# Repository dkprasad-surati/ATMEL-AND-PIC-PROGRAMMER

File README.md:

# ATMEL-AND-PIC-PROGRAMMER
PORTABLE PROGRAMMER

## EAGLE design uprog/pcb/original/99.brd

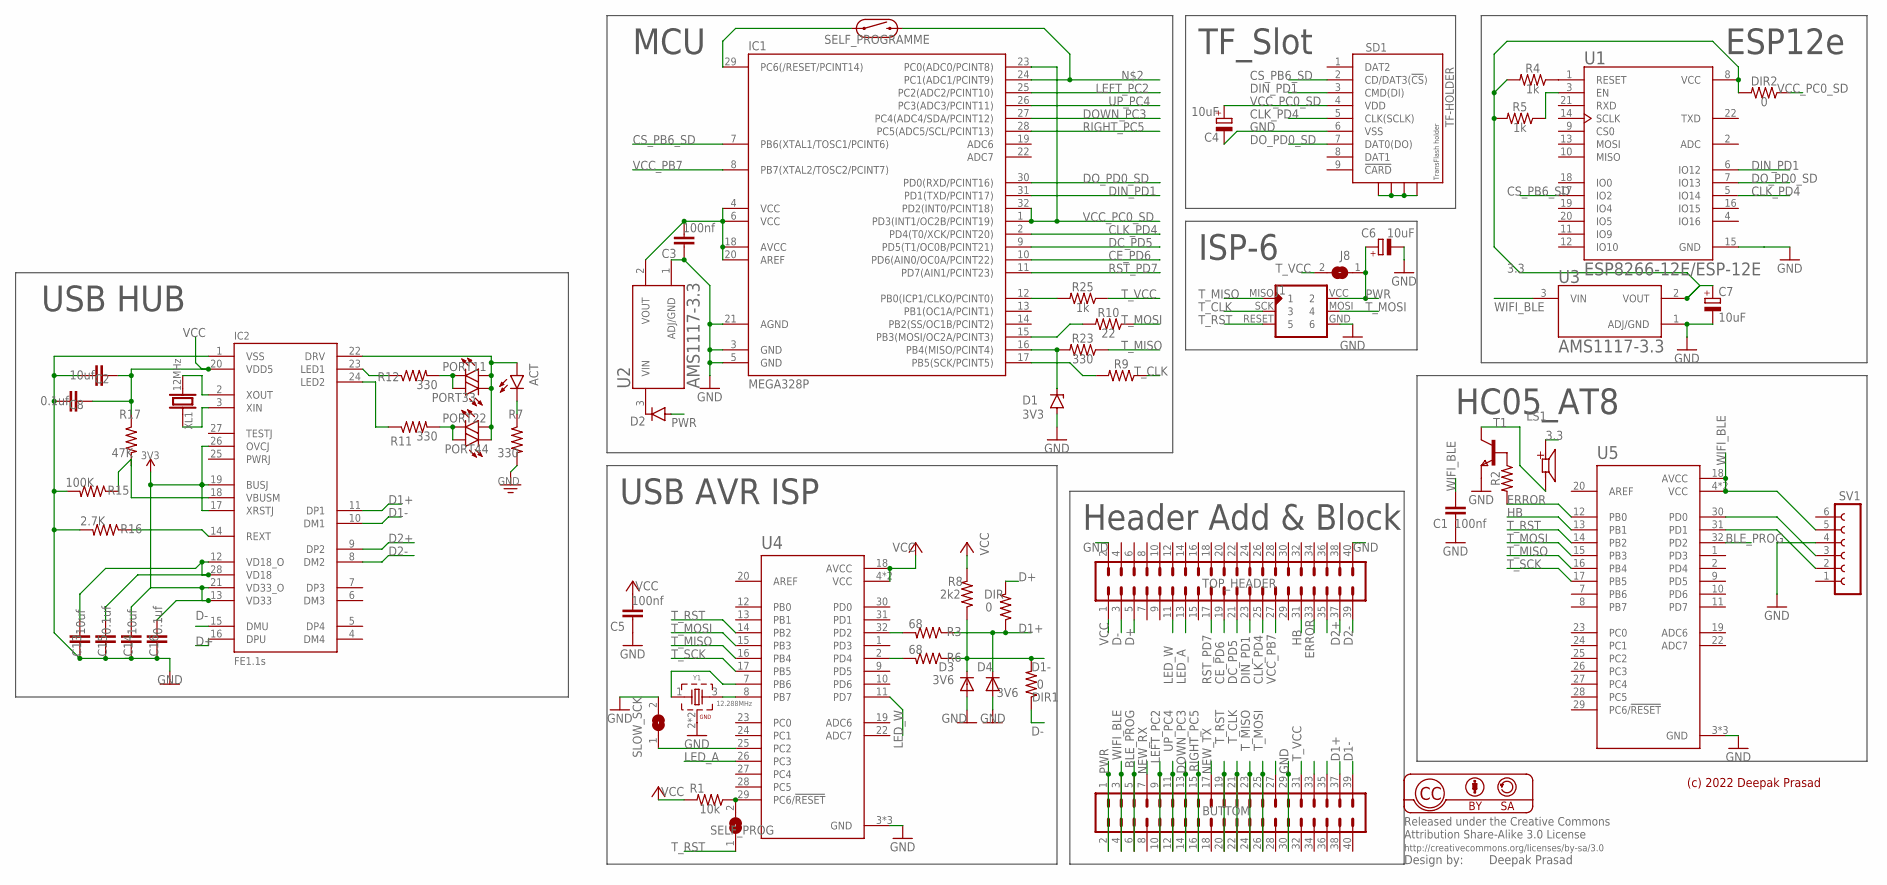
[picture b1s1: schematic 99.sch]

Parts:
ACT: LED1206; LED-1206
BUTTOM: MA20-2
C1, C3, C5: 100nf; C1206
C2, C13, C14: 10uf; C1206
C4, C6, C7: 10uF; C/6032-28R
C8, C15, C16: 0.1uf; C1206
D1: 3V3; SOD80C
D2: DIODE-DO214AC; DO214AC
D3, D4: 3V6; SMA-DIODE
DIR, DIR1, DIR2: 0; RESC3216X70
IC1: MEGA328P; TQFP32-08
IC2: FE1.1S; FE1.1S_SSOP-28
J1: AVR-ISP-6PINAVR-ISP-6PIN; AVR-ISP-6PIN
J8: SJW
LS1: CMT-8530S-SMT; CUI_CMT-8530S-SMT
PORT11, PORT22, PORT33, PORT44: LED1206; LED-1206
R1: 10k; RESC3216X70
R2, R9, R10: 22; RESC3216X70
R3, R6: 68; RESC3216X70
R4, R5, R25: 1k; RESC3216X70
R7, R11, R12, R23: 330; RESC3216X70
R8: 2k2; RESC3216X70
R15: 100K; RESC3216X70
R16: 2.7K; RESC3216X70
R17: 47K; RESC3216X70
SD1: TF-HOLDER; TF-PULL
SELF_PROG: SJW
SELF_PROGRAMME: REED_SWITCH-PTH-GLASS; REED_SWITCH_GLASS
SLOW_SCK: SJW
SV1: FE06-1; FE06
T1: NPNSOT23; SOT-23
TOP_HEADER: MA20-2
U1: ESP8266-12E/ESP-12E; XCVR_ESP8266-12E/ESP-12E
U2, U3: AMS1117-3.3; SOT229P700X180-4N
U4, U5: ATMEGA328P-AU; QFP80P900X900X120-32N
XL1: 12MHz; HC49UP
Y1: 12.288MHz; WE-XTAL_CFPX-104

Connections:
3.3: C7.+, DIR2.2, LS1.P, R4.2, R5.2, U1.8 (VCC), U3.2 (VOUT)
3V3: C14.2, C16.2, IC2.13 (VD33), IC2.17 (XRSTJ), IC2.19 (BUSJ), IC2.21 (VD33_O), IC2.26 (OVCJ)
BLE_PROG: BUTTOM.5, BUTTOM.6, U5.32 (PD2)
CE_PD6: IC1.10 (PD6(AIN0/OC0A/PCINT22)), TOP_HEADER.19
CLK_PD4: IC1.2 (PD4(T0/XCK/PCINT20)), SD1.5 (CLK(SCLK)), TOP_HEADER.25, U1.5 (IO14)
CS_PB6_SD: IC1.7 (PB6(XTAL1/TOSC1/PCINT6)), SD1.2 (CD/DAT3(!CS!)), U1.17 (IO2)
D1+: BUTTOM.37, D4.C, DIR.1, IC2.11 (DP1), R3.1
D1-: BUTTOM.39, D3.C, DIR1.2, IC2.10 (DM1), R6.1, R8.1
D2+: IC2.9 (DP2), TOP_HEADER.37
D2-: IC2.8 (DM2), TOP_HEADER.39
D+: DIR.2, IC2.16 (DPU), TOP_HEADER.5
D-: DIR1.1, IC2.15 (DMU), TOP_HEADER.3
DC_PD5: IC1.9 (PD5(T1/OC0B/PCINT21)), TOP_HEADER.21
DIN_PD1: IC1.31 (PD1(TXD/PCINT17)), SD1.3 (CMD(DI)), TOP_HEADER.23, U1.6 (IO12)
DOWN_PC3: BUTTOM.13, BUTTOM.14, IC1.27 (PC4(ADC4/SDA/PCINT12))
DO_PD0_SD: IC1.30 (PD0(RXD/PCINT16)), SD1.7 (DAT0(DO)), U1.7 (IO13)
ERROR: R2.2, TOP_HEADER.33, U5.12 (PB0)
GND: BUTTOM.29, BUTTOM.30, C1.1, C2.2, C3.1, C4.-, C5.1, C6.-, C7.-, C8.2, C13.1, C14.1, C15.1, C16.1, D1.A, D3.A, D4.A, IC1.3 (GND), IC1.5 (GND), IC1.21 (AGND), IC2.1 (VSS), J1.GND (6), R7.2, R15.2, R16.2, SD1.6 (VSS), SLOW_SCK.2, SV1.4, T1.2 (E), TOP_HEADER.2, TOP_HEADER.40, U1.15 (GND), U2.1 (ADJ/GND), U3.1 (ADJ/GND), U4.3 (GND), U4.5 (GND), U4.21 (GND), U5.3 (GND), U5.5 (GND), U5.21 (GND), Y1.2 (GND), Y1.4 (GND)
GND1: SD1.S1, SD1.S2, SD1.S3, SD1.S4
HB: TOP_HEADER.31, U5.13 (PB1)
LED_A: TOP_HEADER.13, U4.26 (PC3)
LED_W: TOP_HEADER.11, U4.11 (PD7)
LEFT_PC2: BUTTOM.9, BUTTOM.10, IC1.25 (PC2(ADC2/PCINT10))
unnamed: U4.8 (PB7), Y1.3 (2)
unnamed: IC1.24 (PC1(ADC1/PCINT9)), SELF_PROGRAMME.P$2 (2)
unnamed: R4.1, U1.1 (RESET)
unnamed: R2.1, T1.3 (B)
unnamed: R5.1, U1.3 (EN)
unnamed: IC1.12 (PB0(ICP1/CLKO/PCINT0)), R25.2
unnamed: D1.C, IC1.16 (PB4(MISO/PCINT4)), R23.2
unnamed: U4.7 (PB6), Y1.1
unnamed: C3.2, IC1.4 (VCC), IC1.6 (VCC), IC1.18 (AVCC), IC1.20 (AREF), U2.2 (VOUT)
unnamed: R1.1, SELF_PROG.2, U4.29 (PC6/!RESET)
unnamed: D2.C, U2.3 (VIN)
unnamed: IC1.29 (PC6(/RESET/PCINT14)), SELF_PROGRAMME.P$1 (1)
unnamed: SLOW_SCK.1, U4.25 (PC2)
unnamed: SV1.2, U5.31 (PD1)
unnamed: SV1.3, U5.30 (PD0)
unnamed: R3.2, U4.32 (PD2)
unnamed: IC2.14 (REXT), R16.1
unnamed: ACT.C, R7.1
unnamed: R6.2, U4.2 (PD4)
unnamed: C13.2, C15.2, IC2.12 (VD18_O), IC2.28 (VD18)
unnamed: IC1.15 (PB3(MOSI/OC2A/PCINT3)), R10.2
unnamed: IC1.17 (PB5(SCK/PCINT5)), R9.2
unnamed: LS1.N, T1.1 (C)
unnamed: IC2.23 (LED1), R12.1
unnamed: IC2.2 (XOUT), XL1.2
unnamed: IC2.3 (XIN), XL1.1
unnamed: PORT11.C, PORT33.A, R12.2
unnamed: PORT22.C, PORT44.A, R11.2
unnamed: IC2.18 (VBUSM), R15.1, R17.2
unnamed: IC2.24 (LED2), R11.1
unnamed: ACT.A, IC2.22 (DRV), PORT11.A, PORT22.A, PORT33.C, PORT44.C
NEW_RX: BUTTOM.7
NEW_TX: BUTTOM.17
PWR: BUTTOM.1, BUTTOM.2, C6.+, D2.A, J1.VCC (2), J8.1
RIGHT_PC5: BUTTOM.15, BUTTOM.16, IC1.28 (PC5(ADC5/SCL/PCINT13))
RST_PD7: IC1.11 (PD7(AIN1/PCINT23)), TOP_HEADER.17
T_CLK: BUTTOM.21, BUTTOM.22, J1.SCK (3), R9.1
T_MISO: BUTTOM.23, BUTTOM.24, J1.MISO (1), R23.1, U4.16 (PB4), U5.16 (PB4)
T_MOSI: BUTTOM.25, BUTTOM.26, J1.MOSI (4), R10.1, U4.15 (PB3), U5.15 (PB3)
T_RST: BUTTOM.19, BUTTOM.20, J1.RESET (5), SELF_PROG.1, U4.14 (PB2), U5.14 (PB2)
T_SCK: U4.17 (PB5), U5.17 (PB5)
T_VCC: BUTTOM.31, J8.2, R25.1
UP_PC4: BUTTOM.11, BUTTOM.12, IC1.26 (PC3(ADC3/PCINT11))
VCC: C2.1, C5.2, C8.1, IC2.20 (VDD5), R1.2, R8.2, R17.1, TOP_HEADER.1, U4.4 (VCC), U4.6 (VCC), U4.18 (AVCC)
VCC_PB7: IC1.8 (PB7(XTAL2/TOSC2/PCINT7)), TOP_HEADER.27
VCC_PC0_SD: C4.+, DIR2.1, IC1.1 (PD3(INT1/OC2B/PCINT19)), IC1.23 (PC0(ADC0/PCINT8)), IC1.32 (PD2(INT0/PCINT18)), SD1.4 (VDD)
WIFI_BLE: BUTTOM.3, BUTTOM.4, C1.2, SV1.5, U3.3 (VIN), U5.4 (VCC), U5.6 (VCC), U5.18 (AVCC)

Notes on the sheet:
(c) 2022 Deepak Prasad
Header Add & Block
MCU
TF_Slot
ESP12e
ISP-6
USB AVR ISP
HC05_AT8
USB HUB

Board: 2 copper layers, 61 parts (21 on the bottom side), 68 nets, no tracks yet.

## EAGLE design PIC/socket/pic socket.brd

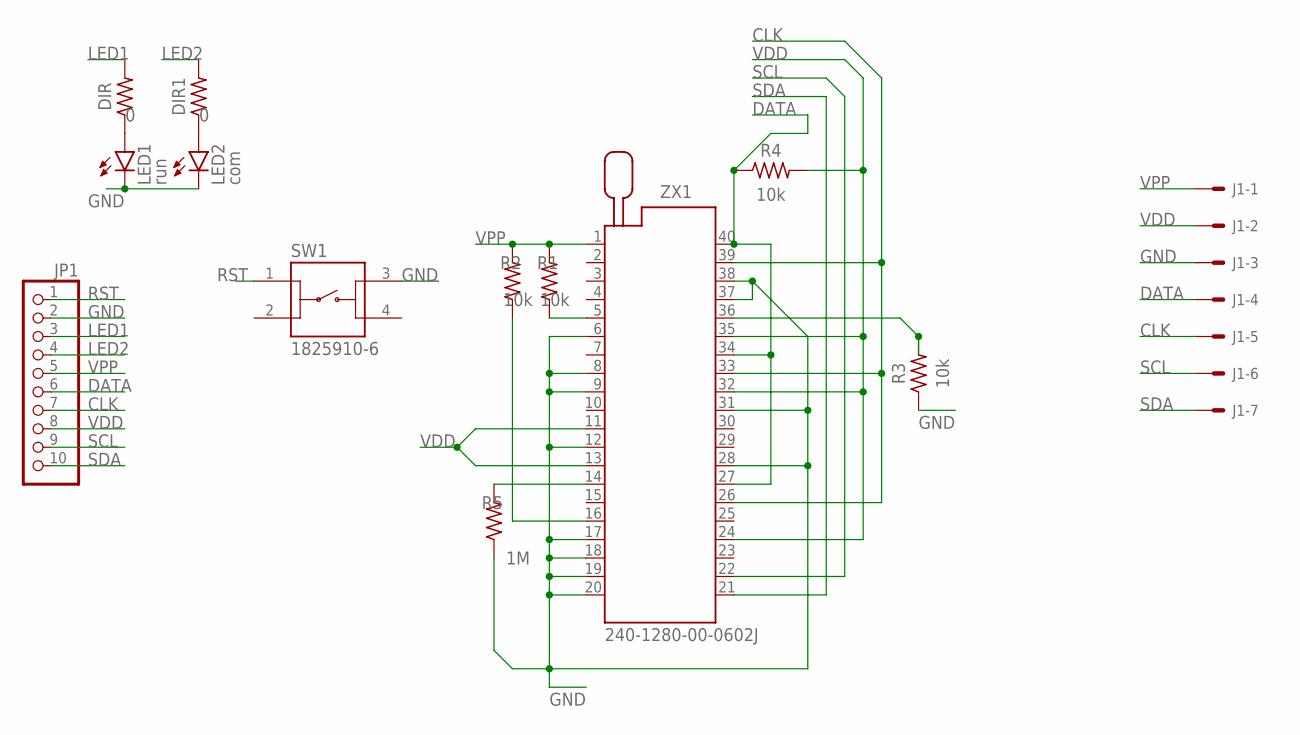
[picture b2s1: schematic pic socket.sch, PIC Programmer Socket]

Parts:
DIR, DIR1: 0; RESC3216X70
J1: 22-05-7078-07; 7395-07
JP1: PINHD-1X10; 1X10
LED1: run; 1206
LED2: com; 1206
R1, R2, R3, R4: 10k; RESC3216X70
R5: 1M; RESC3216X70
SW1: 1825910-6
ZX1: 240-1280-00-0602J

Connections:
CLK: J1.5, JP1.7, ZX1.26, ZX1.33, ZX1.39
DATA: J1.4, JP1.6, R4.1, ZX1.27, ZX1.34, ZX1.40
GND: J1.3, JP1.2, LED1.C, LED2.C, R3.1, R5.1, SW1.3, ZX1.6, ZX1.8, ZX1.9, ZX1.12, ZX1.17, ZX1.18, ZX1.19, ZX1.20, ZX1.28, ZX1.31, ZX1.37, ZX1.38
LED1: DIR.2, JP1.3
LED2: DIR1.2, JP1.4
unnamed: R3.2, ZX1.36
unnamed: R1.1, ZX1.5
unnamed: R2.1, ZX1.16
unnamed: R5.2, ZX1.14
unnamed: DIR.1, LED1.A
unnamed: DIR1.1, LED2.A
RST: JP1.1, SW1.1
SCL: J1.6, JP1.9, ZX1.22
SDA: J1.7, JP1.10, ZX1.21
VDD: J1.2, JP1.8, R4.2, ZX1.11, ZX1.13, ZX1.24, ZX1.32, ZX1.35
VPP: J1.1, JP1.5, R1.2, R2.2, ZX1.1

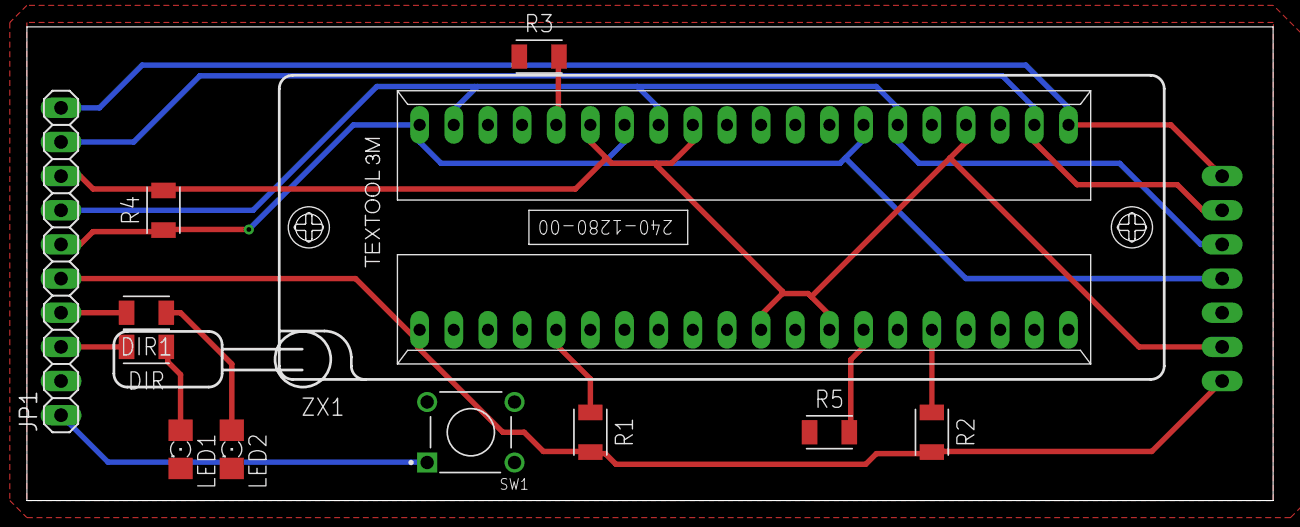
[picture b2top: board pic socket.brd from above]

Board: 2 copper layers, 92.7 x 35.2 mm, 13 parts (1 on the bottom side), 16 nets.

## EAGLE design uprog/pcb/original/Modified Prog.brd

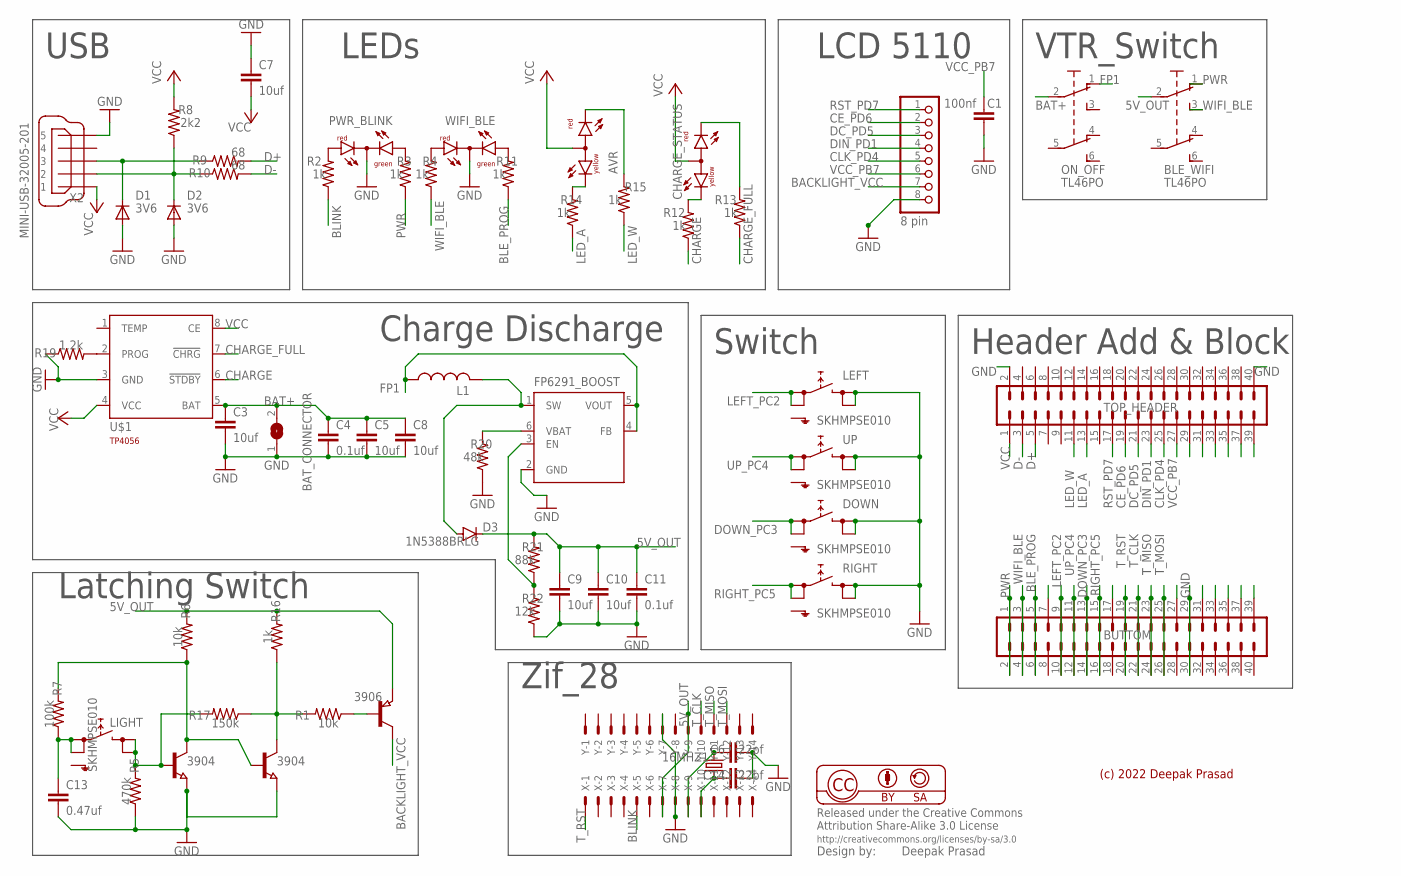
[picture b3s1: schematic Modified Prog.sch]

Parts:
16MHZ1: CSM-7X-DU
3906: PNP-TRANSISTOR_SOT23; SOT23
AVR: DUOLED-RY-A; DUOLED-A-5MM
BAT_CONNECTOR: SJW
BLE_WIFI: TL46PO; TL4XPO
BUTTOM: MA20-2
C1: 100nf; C1206
C3, C5, C7, C8, C9, C10: 10uf; C1206
C4, C11: 0.1uf; C1206
C6, C14: 22pf; C1206
C13: 0.47uf; C1206
CHARGE_STATUS: DUOLED-RY-A; DUOLED-A-5MM
D1, D2: 3V6; SMA-DIODE
D3: 1N5388BRLG; SMC
DOWN: SKHMPSE010; SKHMPXE010
FP6291_BOOST: TPS61070DDC; TSOT23-6_DDC
JP1: 8 pin; 1X08
L1: L-USPIS2816; PIS2816
LEFT: SKHMPSE010; SKHMPXE010
LIGHT: SKHMPSE010; SKHMPXE010
ON_OFF: TL46PO; TL4XPO
PWR_BLINK: DUOLED-RG-C; DUOLED-C-5MM
Q2, Q3: 3904; SOT23
R1, R6: 10k; RESC3216X70
R2, R3, R4, R11, R12, R13, R14, R15, R16: 1k; RESC3216X70
R5: 470k; RESC3216X70
R7: 100k; RESC3216X70
R8: 2k2; RESC3216X70
R9, R10: 68; RESC3216X70
R17: 150k; RESC3216X70
R19: 1.2k; RESC3216X70
R20: 48k; RESC3216X70
R21: 88k; RESC3216X70
R22: 12k; RESC3216X70
RIGHT: SKHMPSE010; SKHMPXE010
TOP_HEADER: MA20-2
U$1: TP4056; SOT23-8
UP: SKHMPSE010; SKHMPXE010
WIFI_BLE: DUOLED-RG-C; DUOLED-C-5MM
X: C-GRID-14-70543; 70543-14
X2: MINI-USB-32005-201; 32005-201
Y: C-GRID-14-70543; 70543-14

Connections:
5V_OUT: 3906.2 (E), BLE_WIFI.2, C9.1, C10.1, C11.1, D3.C, R6.2, R16.2, R21.2, X.7, Y.9
BACKLIGHT_VCC: 3906.3 (C), JP1.7
BAT+: BAT_CONNECTOR.2, C3.1, C4.1, C5.1, C8.1, ON_OFF.2, U$1.5 (BAT)
BLE_PROG: BUTTOM.5, BUTTOM.6, R11.1
BLINK: R2.1, X.5
CE_PD6: JP1.2, TOP_HEADER.19
CHARGE: R12.1, U$1.6 (!STDBY)
CHARGE_FULL: R13.1, U$1.7 (!CHRG)
CLK_PD4: JP1.5, TOP_HEADER.25
D+: R9.2, TOP_HEADER.5
D-: R10.2, TOP_HEADER.3
DC_PD5: JP1.3, TOP_HEADER.21
DIN_PD1: JP1.4, TOP_HEADER.23
DOWN_PC3: BUTTOM.13, BUTTOM.14, DOWN.1 (1.1), DOWN.2 (1.2)
FP1: FP6291_BOOST.4 (FB), FP6291_BOOST.5 (VOUT), L1.1, ON_OFF.1 (O)
GND: BAT_CONNECTOR.1, BUTTOM.29, BUTTOM.30, C1.1, C3.2, C4.2, C5.2, C6.2, C7.1, C8.2, C9.2, C10.2, C11.2, C13.2, C14.2, D1.A, D2.A, DOWN.3 (2.1), DOWN.4 (2.2), FP6291_BOOST.2 (GND), JP1.8, LEFT.3 (2.1), LEFT.4 (2.2), PWR_BLINK.C, Q2.2 (E), Q3.2 (E), R5.1, R19.1, R20.1, R22.1, RIGHT.3 (2.1), RIGHT.4 (2.2), TOP_HEADER.2, TOP_HEADER.40, U$1.3 (GND), UP.3 (2.1), UP.4 (2.2), WIFI_BLE.C, X.8, X2.5, Y.7
LED_A: R14.1, TOP_HEADER.13
LED_W: R15.1, TOP_HEADER.11
LEFT_PC2: BUTTOM.9, BUTTOM.10, LEFT.1 (1.1), LEFT.2 (1.2)
unnamed: PWR_BLINK.AR, R2.2
unnamed: PWR_BLINK.AX (AG), R3.2
unnamed: R4.2, WIFI_BLE.AR
unnamed: R11.2, WIFI_BLE.AX (AG)
unnamed: 3906.1 (B), R1.1
unnamed: D1.C, R9.1, X2.3
unnamed: D2.C, R8.1, R10.1, X2.2
unnamed: C13.1, LIGHT.1 (1.1), LIGHT.2 (1.2), R7.1
unnamed: LIGHT.3 (2.1), LIGHT.4 (2.2), Q2.1 (B), R5.2, R17.2
unnamed: CHARGE_STATUS.CX (CY), R12.2
unnamed: 16MHZ1.2, C6.1, X.9, Y.13
unnamed: R19.2, U$1.2 (PROG)
unnamed: AVR.CX (CY), R14.2
unnamed: CHARGE_STATUS.CR, R13.2
unnamed: AVR.CR, R15.2
unnamed: Q3.3 (C), R1.2, R16.1, R17.1
unnamed: D3.A, FP6291_BOOST.1 (SW), L1.2
unnamed: FP6291_BOOST.6 (VBAT), R20.2
unnamed: Q2.3 (C), Q3.1 (B), R6.1, R7.2
unnamed: FP6291_BOOST.3 (EN), R21.1, R22.2
unnamed: 16MHZ1.1, C14.1, X.10
PWR: BLE_WIFI.1 (O), BUTTOM.1, BUTTOM.2, R3.1
RIGHT_PC5: BUTTOM.15, BUTTOM.16, RIGHT.1 (1.1), RIGHT.2 (1.2)
RST_PD7: JP1.1, TOP_HEADER.17
T_CLK: BUTTOM.21, BUTTOM.22, Y.10
T_MISO: BUTTOM.23, BUTTOM.24, Y.11
T_MOSI: BUTTOM.25, BUTTOM.26, Y.12
T_RST: BUTTOM.19, BUTTOM.20, X.1
UP_PC4: BUTTOM.11, BUTTOM.12, UP.1 (1.1), UP.2 (1.2)
VCC: AVR.A, C7.2, CHARGE_STATUS.A, R8.2, TOP_HEADER.1, U$1.4 (VCC), U$1.8 (CE), X2.1
VCC_PB7: C1.2, JP1.6, TOP_HEADER.27
WIFI_BLE: BLE_WIFI.3 (S), BUTTOM.3, BUTTOM.4, R4.1

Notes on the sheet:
(c) 2022 Deepak Prasad
Zif_28
USB
LEDs
Charge Discharge
Switch
LCD 5110
VTR_Switch
Latching Switch
Header Add & Block

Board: 2 copper layers, 61 parts (29 on the bottom side), 51 nets, no tracks yet.

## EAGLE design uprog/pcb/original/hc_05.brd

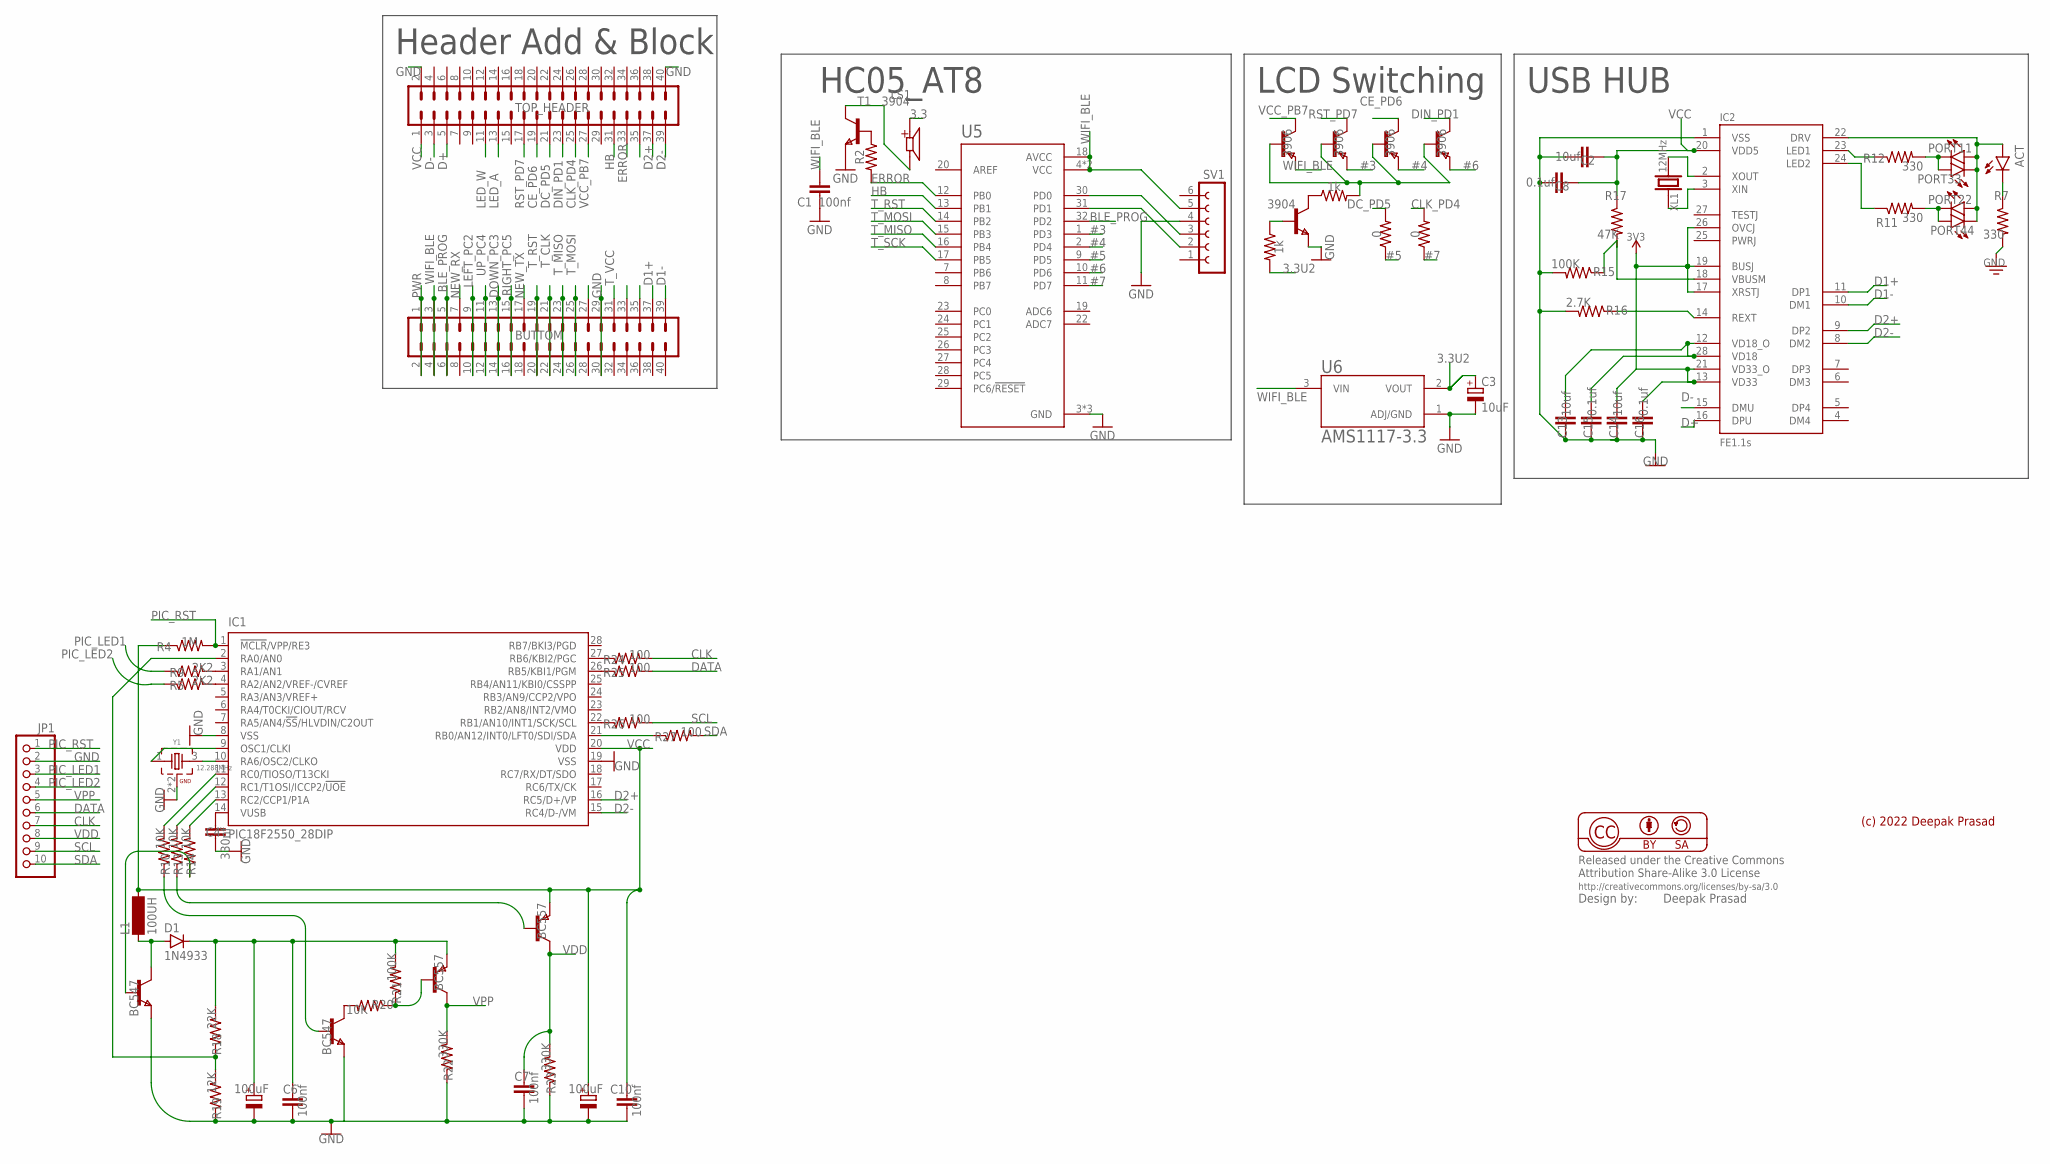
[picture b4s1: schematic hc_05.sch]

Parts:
ACT: LED1206; LED-1206
BUTTOM: MA20-2
C1, C6, C7, C10: 100nf; C1206
C2, C13, C14: 10uf; C1206
C3: 10uF; C/6032-28R
C4: 330nf; C1206
C5, C9: 100uF; C/6032-28R
C8, C15, C16: 0.1uf; C1206
D1: 1N4933; SMB
IC1: PIC18F2550_28DIP; DIL28-3
IC2: FE1.1S; FE1.1S_SSOP-28
JP1: PINHD-1X10; 1X10
L1: 100UH; MS85
LS1: CMT-8530S-SMT; CUI_CMT-8530S-SMT
PORT11, PORT22, PORT33, PORT44: LED1206; LED-1206
R1, R6: 1k; RESC3216X70
R2: 22; RESC3216X70
R3, R8: 0; RESC3216X70
R4: 1M; RESC3216X70
R5, R9: 2K2; RESC3216X70
R7, R11, R12: 330; RESC3216X70
R10, R13, R14, R20: 10K; RESC3216X70
R15, R21: 100K; RESC3216X70
R16: 2.7K; RESC3216X70
R17: 47K; RESC3216X70
R18: 22K; RESC3216X70
R19: 12K; RESC3216X70
R22, R23: 330K; RESC3216X70
R24, R25, R26, R27: 100; RESC3216X70
SV1: FE06-1; FE06
T1, T2: 3904; SOT-23
T3, T4, T5, T6: 3906; SOT-23
T7, T9: BC547; SOT-23
T8, T10: BC557; SOT-23
TOP_HEADER: MA20-2
U5: ATMEGA328P-AU; QFP80P900X900X120-32N
U6: AMS1117-3.3; SOT229P700X180-4N
XL1: 12MHz; HC49UP
Y1: 12.288MHz; WE-XTAL_CFPX-104

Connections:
3.3: LS1.P
3.3U2: C3.+, R6.2, U6.2 (VOUT)
3V3: C14.2, C16.2, IC2.13 (VD33), IC2.17 (XRSTJ), IC2.19 (BUSJ), IC2.21 (VD33_O), IC2.26 (OVCJ)
#3: T4.2 (E), U5.1 (PD3)
#4: T5.2 (E), U5.2 (PD4)
#5: R8.1, U5.9 (PD5)
#6: T6.2 (E), U5.10 (PD6)
#7: R3.1, U5.11 (PD7)
BLE_PROG: BUTTOM.5, BUTTOM.6, U5.32 (PD2)
CE_PD6: T5.1 (C), TOP_HEADER.19
CLK: JP1.7, R24.2
CLK_PD4: R3.2, TOP_HEADER.25
D1+: BUTTOM.37, IC2.11 (DP1)
D1-: BUTTOM.39, IC2.10 (DM1)
D2+: IC1.16 (RC5/D+/VP), IC2.9 (DP2), TOP_HEADER.37
D2-: IC1.15 (RC4/D-/VM), IC2.8 (DM2), TOP_HEADER.39
D+: IC2.16 (DPU), TOP_HEADER.5
D-: IC2.15 (DMU), TOP_HEADER.3
DATA: JP1.6, R25.2
DC_PD5: R8.2, TOP_HEADER.21
DIN_PD1: T6.1 (C), TOP_HEADER.23
DOWN_PC3: BUTTOM.13, BUTTOM.14
ERROR: R2.2, TOP_HEADER.33, U5.12 (PB0)
GND: BUTTOM.29, BUTTOM.30, C1.1, C2.2, C3.-, C4.1, C5.-, C6.1, C7.1, C8.2, C9.-, C10.1, C13.1, C14.1, C15.1, C16.1, IC1.8 (VSS), IC1.19 (VSS), IC2.1 (VSS), JP1.2, R7.2, R15.2, R16.2, R19.1, R22.1, R23.1, SV1.4, T1.2 (E), T2.2 (E), T7.2 (E), T9.2 (E), TOP_HEADER.2, TOP_HEADER.40, U5.3 (GND), U5.5 (GND), U5.21 (GND), U6.1 (ADJ/GND), Y1.2 (GND), Y1.4 (GND)
HB: TOP_HEADER.31, U5.13 (PB1)
LED_A: TOP_HEADER.13
LED_W: TOP_HEADER.11
LEFT_PC2: BUTTOM.9, BUTTOM.10
unnamed: R1.1, T2.1 (C)
unnamed: R1.2, T3.3 (B), T4.3 (B), T5.3 (B), T6.3 (B)
unnamed: IC1.27 (RB6/KBI2/PGC), R24.1
unnamed: R2.1, T1.3 (B)
unnamed: IC1.4 (RA2/AN2/VREF-/CVREF), R5.2
unnamed: IC1.3 (RA1/AN1), R9.2
unnamed: IC1.9 (OSC1/CLKI), Y1.1
unnamed: IC1.10 (RA6/OSC2/CLKO), Y1.3 (2)
unnamed: IC1.11 (RC0/TIOSO/T13CKI), R10.2
unnamed: IC1.12 (RC1/T1OSI/ICCP2/!UOE), R13.2
unnamed: IC1.13 (RC2/CCP1/P1A), R14.2
unnamed: C4.2, IC1.14 (VUSB)
unnamed: R10.1, T9.3 (B)
unnamed: SV1.2, U5.31 (PD1)
unnamed: SV1.3, U5.30 (PD0)
unnamed: R6.1, T2.3 (B)
unnamed: IC2.14 (REXT), R16.1
unnamed: ACT.C, R7.1
unnamed: D1.2 (A), L1.1, T7.1 (C)
unnamed: C13.2, C15.2, IC2.12 (VD18_O), IC2.28 (VD18)
unnamed: C5.+, C6.2, D1.1 (C), R18.2, R21.2, T10.2 (E)
unnamed: R14.1, T7.3 (B)
unnamed: LS1.N, T1.1 (C)
unnamed: IC2.23 (LED1), R12.1
unnamed: IC2.2 (XOUT), XL1.2
unnamed: IC2.3 (XIN), XL1.1
unnamed: PORT11.C, PORT33.A, R12.2
unnamed: PORT22.C, PORT44.A, R11.2
unnamed: IC1.2 (RA0/AN0), R18.1, R19.2
unnamed: R13.1, T8.3 (B)
unnamed: R20.2, T9.1 (C)
unnamed: R20.1, R21.1, T10.3 (B)
unnamed: IC1.26 (RB5/KBI1/PGM), R25.1
unnamed: IC1.22 (RB1/AN10/INT1/SCK/SCL), R26.1
unnamed: IC1.21 (RB0/AN12/INT0/LFT0/SDI/SDA), R27.1
unnamed: IC2.18 (VBUSM), R15.1, R17.2
unnamed: IC2.24 (LED2), R11.1
unnamed: ACT.A, IC2.22 (DRV), PORT11.A, PORT22.A, PORT33.C, PORT44.C
NEW_RX: BUTTOM.7
NEW_TX: BUTTOM.17
PIC_LED1: JP1.3, R9.1
PIC_LED2: JP1.4, R5.1
PIC_RST: IC1.1 (!MCLR!/VPP/RE3), JP1.1, R4.2
PWR: BUTTOM.1, BUTTOM.2
RIGHT_PC5: BUTTOM.15, BUTTOM.16
RST_PD7: T4.1 (C), TOP_HEADER.17
SCL: JP1.9, R26.2
SDA: JP1.10, R27.2
T_CLK: BUTTOM.21, BUTTOM.22
T_MISO: BUTTOM.23, BUTTOM.24, U5.16 (PB4)
T_MOSI: BUTTOM.25, BUTTOM.26, U5.15 (PB3)
T_RST: BUTTOM.19, BUTTOM.20, U5.14 (PB2)
T_SCK: U5.17 (PB5)
T_VCC: BUTTOM.31
UP_PC4: BUTTOM.11, BUTTOM.12
VCC: C2.1, C8.1, C9.+, C10.2, IC1.20 (VDD), IC2.20 (VDD5), L1.2, R4.1, R17.1, T8.2 (E), TOP_HEADER.1
VCC_PB7: T3.1 (C), TOP_HEADER.27
VDD: C7.2, JP1.8, R23.2, T8.1 (C)
VPP: JP1.5, R22.2, T10.1 (C)
WIFI_BLE: BUTTOM.3, BUTTOM.4, C1.2, SV1.5, T3.2 (E), U5.4 (VCC), U5.6 (VCC), U5.18 (AVCC), U6.3 (VIN)

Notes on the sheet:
(c) 2022 Deepak Prasad
Header Add & Block
HC05_AT8
USB HUB
LCD Switching

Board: 2 copper layers, 69 parts (29 on the bottom side), 81 nets, no tracks yet.

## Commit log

2023-10-28 files

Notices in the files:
parts and their libraries:
Wurth_Quartz Crystals: Copyright: Würth Elektronik
SparkFun-Switches: Licensing: Creative Commons ShareAlike 4.0 International - https://creativecommons.org/licenses/by-sa/4.0
balto: Released under the Creative Commons
balto: http://creativecommons.org/licenses/by-sa/3.0
